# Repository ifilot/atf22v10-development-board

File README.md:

# ATF22V10 DEVELOPMENT BOARD

PCB and firmware to program the ATF22V10 SPLD.

## Compilation

For flashing the SPLD, we make use of
[galette](https://github.com/simon-frankau/galette). This repository is
available in this folder as submodule, which you need to sync via

```bash
git submodule update --init --recursive
```

Next, to create the `galette` executable, follow the instructions below.

```bash
sudo apt install build-essential cargo rustup
cd galette/src
cargo build --release
```

The executable resides in `./target/release/galette`.

## Creating JED files

Construct a `.pld` file and move to the folder in which the file resides.
Next, run

```bash
../../galette/target/release/galette example.pld
```

For some of the examples provides under [plds](plds), there are also Makefiles
available.

Next, the resulting `.jed` file can be flashed onto the `ATF22V10` chip
using a compatible chip flasher such as the TL866II+.

> [!WARNING]  
> According to the [datasheet](https://ww1.microchip.com/downloads/en/DeviceDoc/doc0735.pdf),
> the `ATF22V10` chips have a limited number (i.e. 100) of erase/write cycles.

> [!TIP]  
> For verification purposes, *deselect* `Encrypt Chip`.

> [!NOTES]  
> The ATF22V10 has *weak sourcing capacity*, meaning it can only drive about 4mA
> of current. It however has *strong sinking capacity*.

## Logic equations

| Symbol | Operation |
|--------|-----------|
| `*`    | AND       |
| `+`    | OR        |
| `!`    | NOT       |

## Relevant links

* https://mike42.me/blog/2021-10-programming-plds-with-open-source-software

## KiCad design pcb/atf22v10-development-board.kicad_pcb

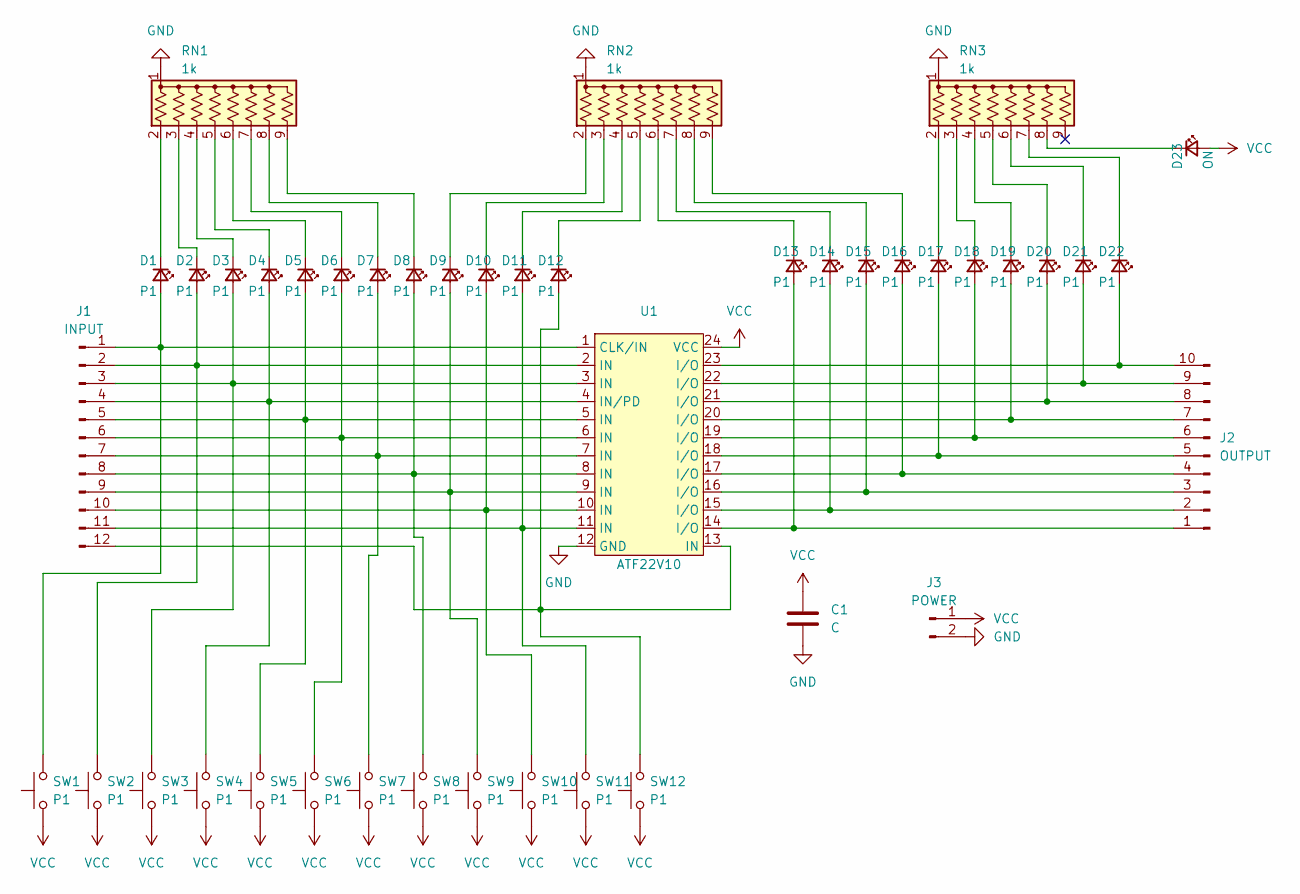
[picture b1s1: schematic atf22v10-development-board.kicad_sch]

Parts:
C1: C; C_Disc_D5.0mm_W2.5mm_P2.50mm
D1, D2, D3, D4, D5, D6, D7, D8, D9, D10, D11, D12, D13, D14, D15, D16, D17, D18, D19, D20, D21, D22: P1; LED_D5.0mm
D23: ON; LED_D5.0mm
J1: INPUT; PinSocket_1x12_P2.54mm_Vertical
J2: OUTPUT; PinSocket_1x10_P2.54mm_Vertical
J3: POWER; PinSocket_1x02_P2.54mm_Vertical
RN1, RN2, RN3: 1k; R_Array_SIP9
SW1, SW2, SW3, SW4, SW5, SW6, SW7, SW8, SW9, SW10, SW11, SW12: P1; SW_PUSH_6mm
U1: ATF22V10; DIP-24_W7.62mm_Socket

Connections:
GND: C1.1, J3.2, RN1.1 (common), RN2.1 (common), RN3.1 (common), U1.12 (GND)
unnamed: D1.2 (A), J1.1, SW1.2, U1.1 (CLK/IN)
unnamed: D1.1 (K), RN1.2 (R1)
unnamed: D2.2 (A), J1.2, SW2.2, U1.2 (IN)
unnamed: D2.1 (K), RN1.3 (R2)
unnamed: D3.2 (A), J1.3, SW3.2, U1.3 (IN)
unnamed: D3.1 (K), RN1.4 (R3)
unnamed: D4.2 (A), J1.4, SW4.2, U1.4 (IN/PD)
unnamed: D4.1 (K), RN1.5 (R4)
unnamed: D5.2 (A), J1.5, SW5.2, U1.5 (IN)
unnamed: D5.1 (K), RN1.6 (R5)
unnamed: D6.2 (A), J1.6, SW6.2, U1.6 (IN)
unnamed: D6.1 (K), RN1.7 (R6)
unnamed: D7.2 (A), J1.7, SW7.2, U1.7 (IN)
unnamed: D7.1 (K), RN1.8 (R7)
unnamed: D8.2 (A), J1.8, SW8.2, U1.8 (IN)
unnamed: D8.1 (K), RN1.9 (R8)
unnamed: D9.2 (A), J1.9, SW9.2, U1.9 (IN)
unnamed: D9.1 (K), RN2.2 (R1)
unnamed: D10.2 (A), J1.10, SW10.2, U1.10 (IN)
unnamed: D10.1 (K), RN2.3 (R2)
unnamed: D11.2 (A), J1.11, SW11.2, U1.11 (IN)
unnamed: D11.1 (K), RN2.4 (R3)
unnamed: D12.2 (A), J1.12, SW12.2, U1.13 (IN)
unnamed: D12.1 (K), RN2.5 (R4)
unnamed: D13.2 (A), J2.1, U1.14 (I/O)
unnamed: D13.1 (K), RN2.6 (R5)
unnamed: D14.2 (A), J2.2, U1.15 (I/O)
unnamed: D14.1 (K), RN2.7 (R6)
unnamed: D15.2 (A), J2.3, U1.16 (I/O)
unnamed: D15.1 (K), RN2.8 (R7)
unnamed: D16.2 (A), J2.4, U1.17 (I/O)
unnamed: D16.1 (K), RN2.9 (R8)
unnamed: D17.2 (A), J2.5, U1.18 (I/O)
unnamed: D17.1 (K), RN3.2 (R1)
unnamed: D18.2 (A), J2.6, U1.19 (I/O)
unnamed: D18.1 (K), RN3.3 (R2)
unnamed: D19.2 (A), J2.7, U1.20 (I/O)
unnamed: D19.1 (K), RN3.4 (R3)
unnamed: D20.2 (A), J2.8, U1.21 (I/O)
unnamed: D20.1 (K), RN3.5 (R4)
unnamed: D21.2 (A), J2.9, U1.22 (I/O)
unnamed: D21.1 (K), RN3.6 (R5)
unnamed: D22.2 (A), J2.10, U1.23 (I/O)
unnamed: D22.1 (K), RN3.7 (R6)
unnamed: D23.1 (K), RN3.8 (R7)
VCC: C1.2, D23.2 (A), J3.1, SW1.1, SW2.1, SW3.1, SW4.1, SW5.1, SW6.1, SW7.1, SW8.1, SW9.1, SW10.1, SW11.1, SW12.1, U1.24 (VCC)

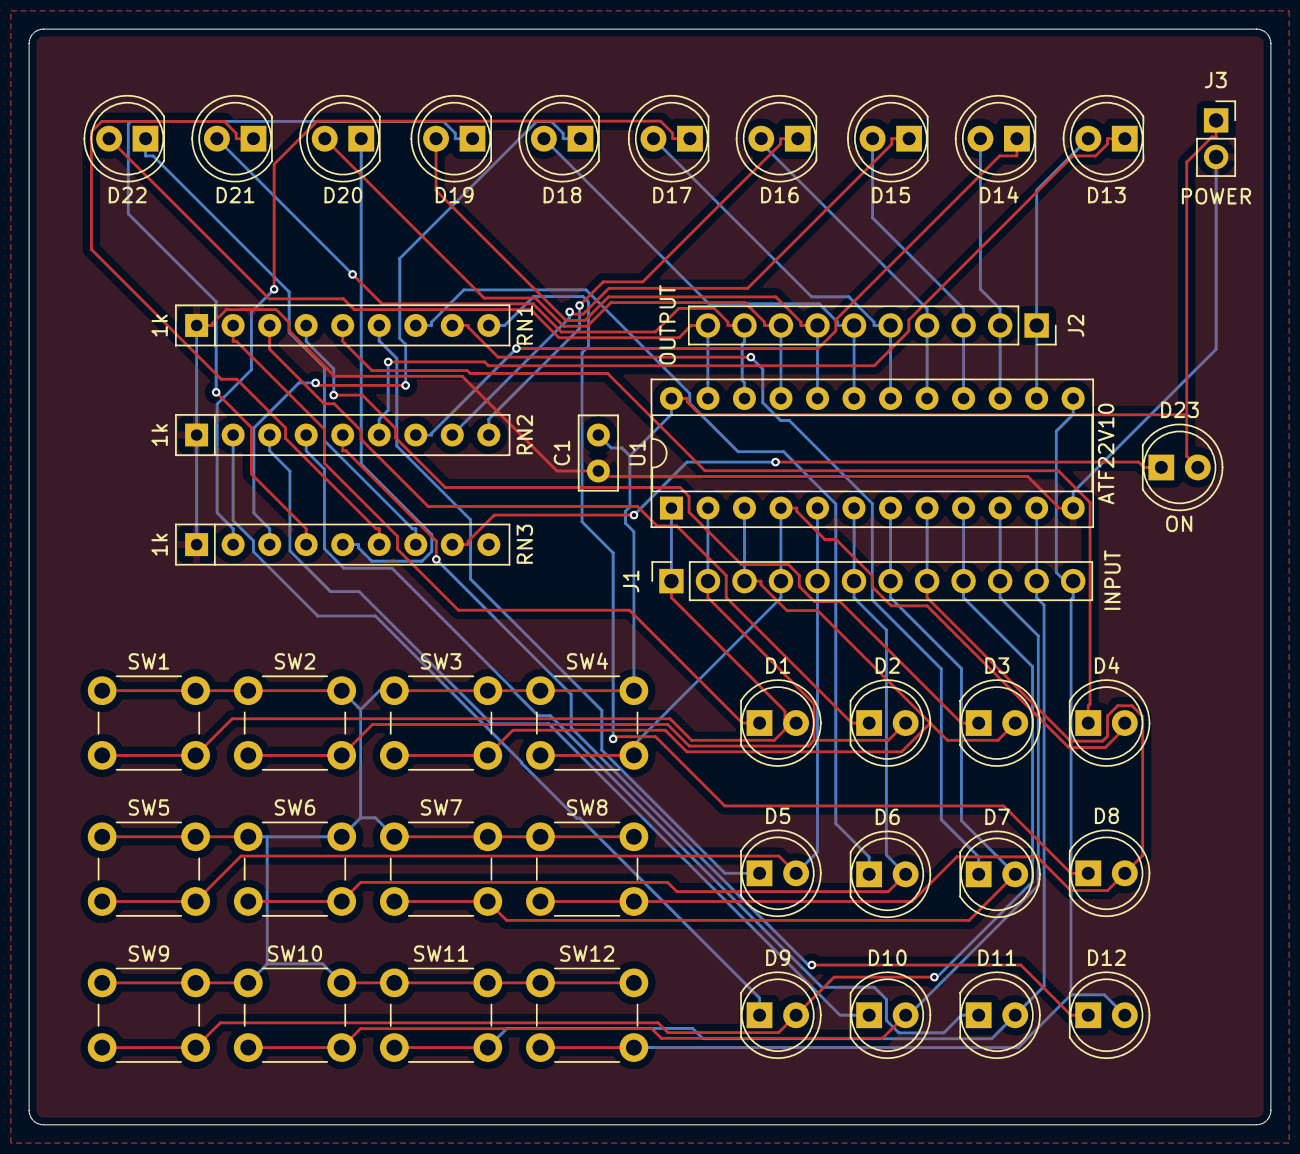
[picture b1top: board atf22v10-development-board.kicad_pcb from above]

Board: 2 copper layers, 86.4 x 76.2 mm, 43 parts (0 on the bottom side), 47 nets.

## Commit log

2025-03-02 Changing names for examples
2025-03-02 Adding example for a memory map
